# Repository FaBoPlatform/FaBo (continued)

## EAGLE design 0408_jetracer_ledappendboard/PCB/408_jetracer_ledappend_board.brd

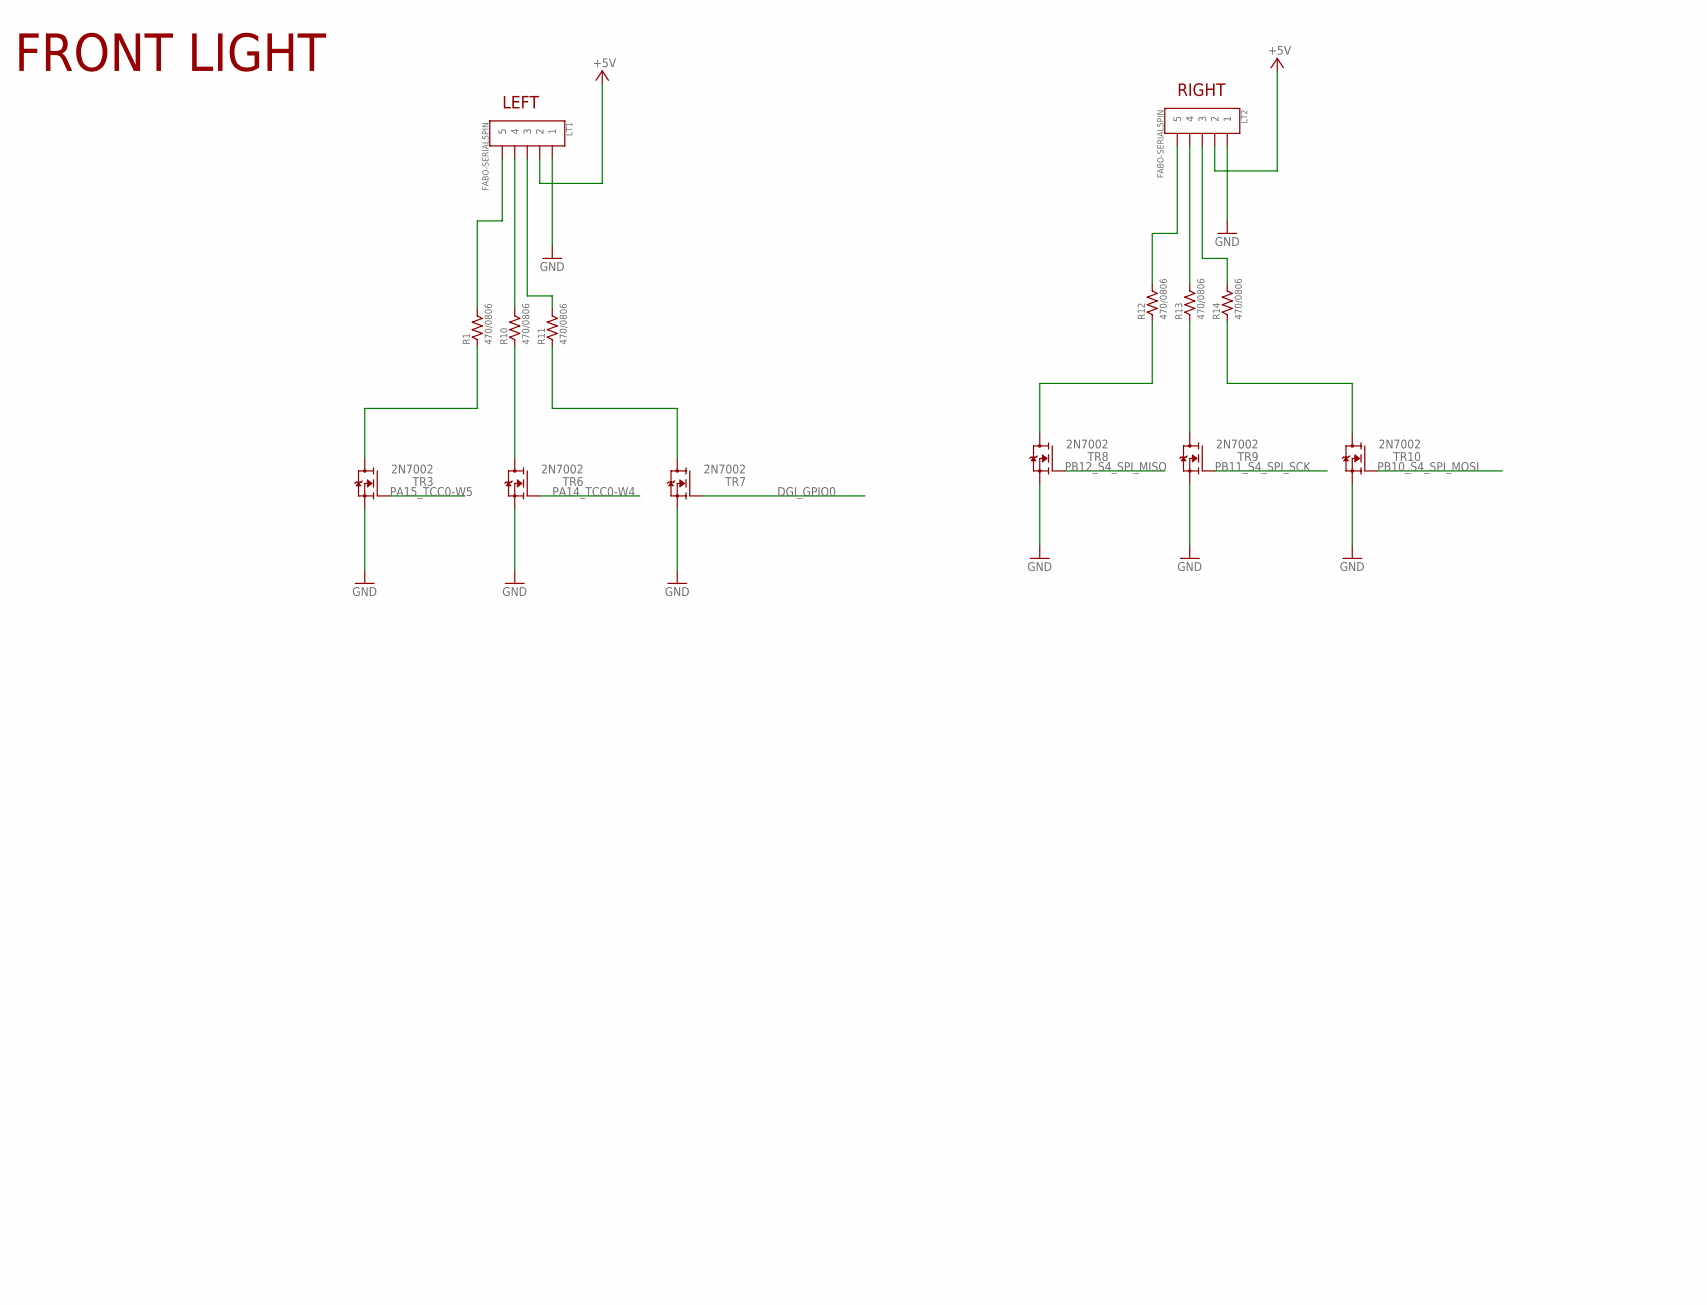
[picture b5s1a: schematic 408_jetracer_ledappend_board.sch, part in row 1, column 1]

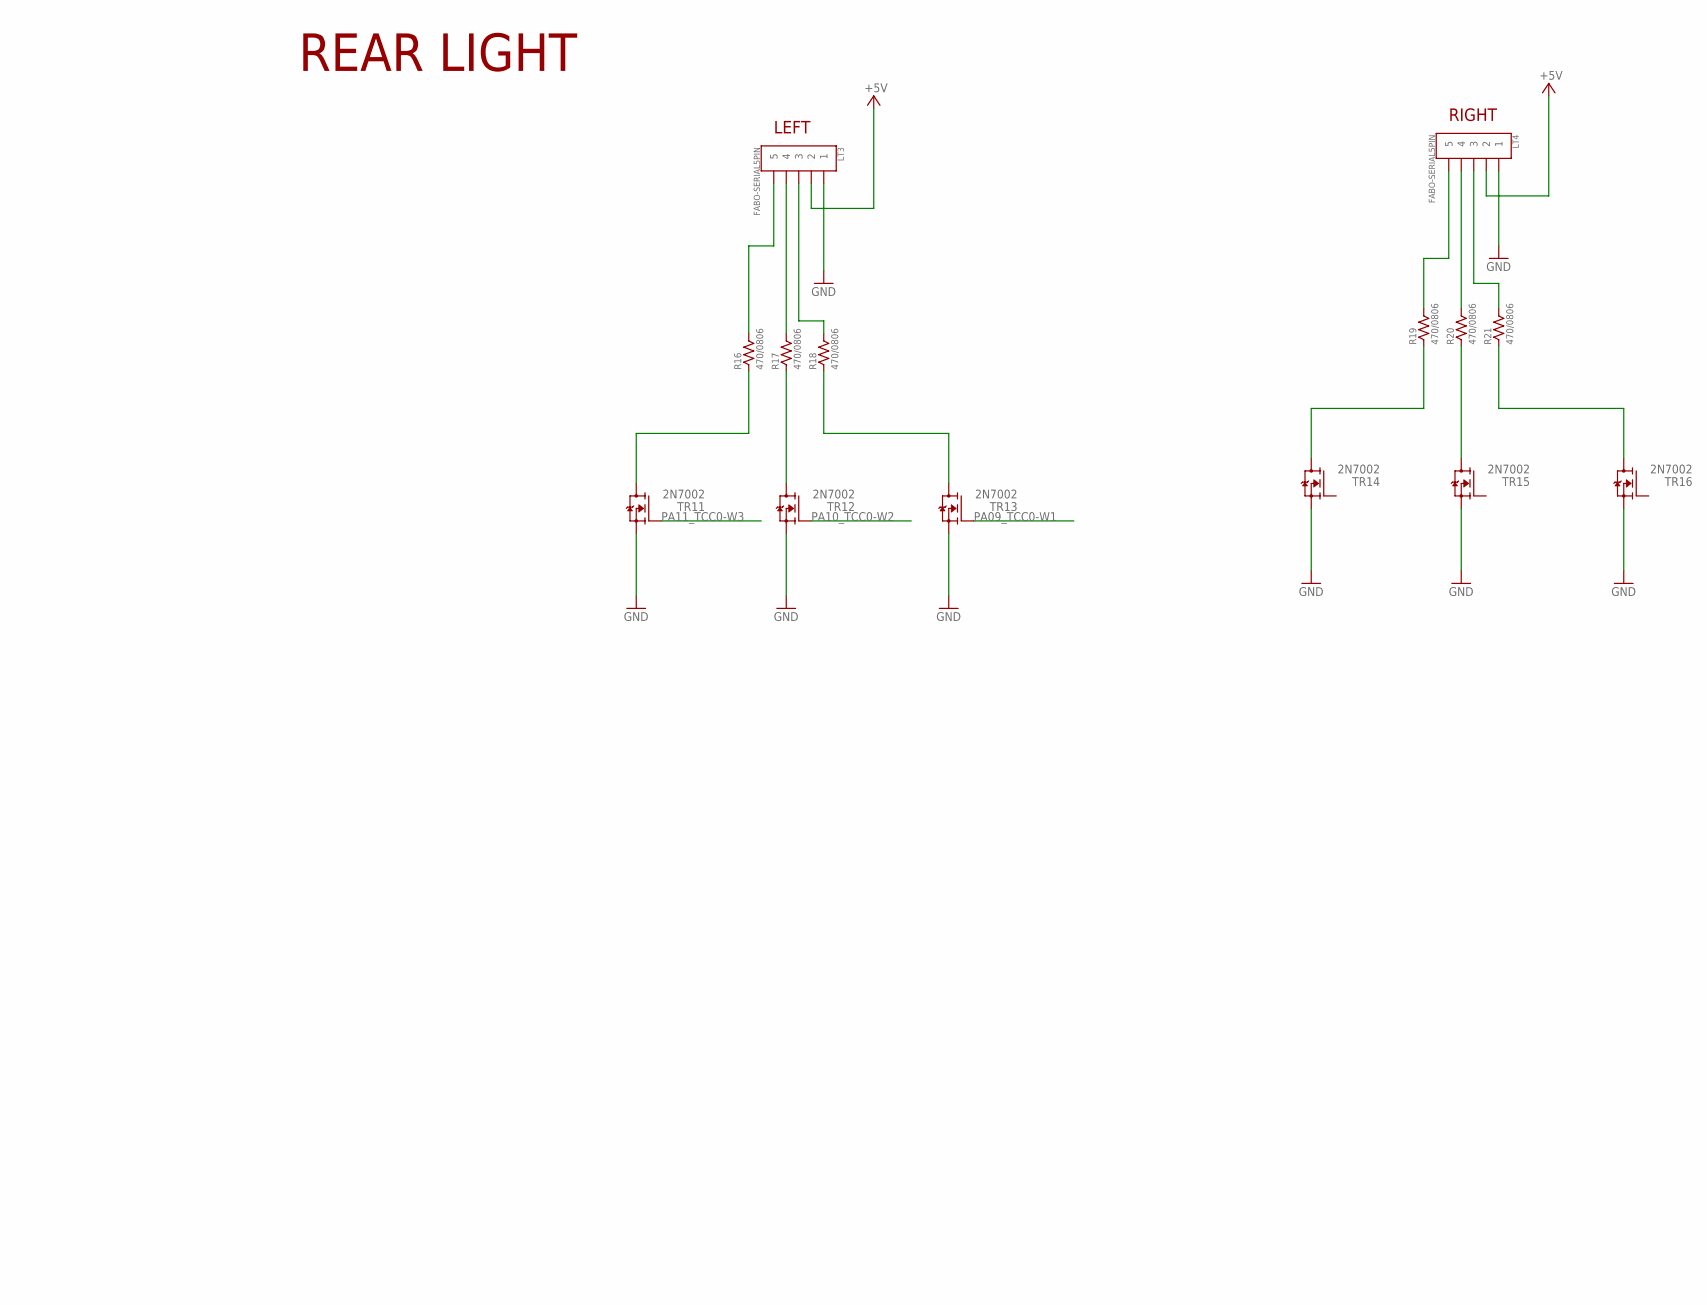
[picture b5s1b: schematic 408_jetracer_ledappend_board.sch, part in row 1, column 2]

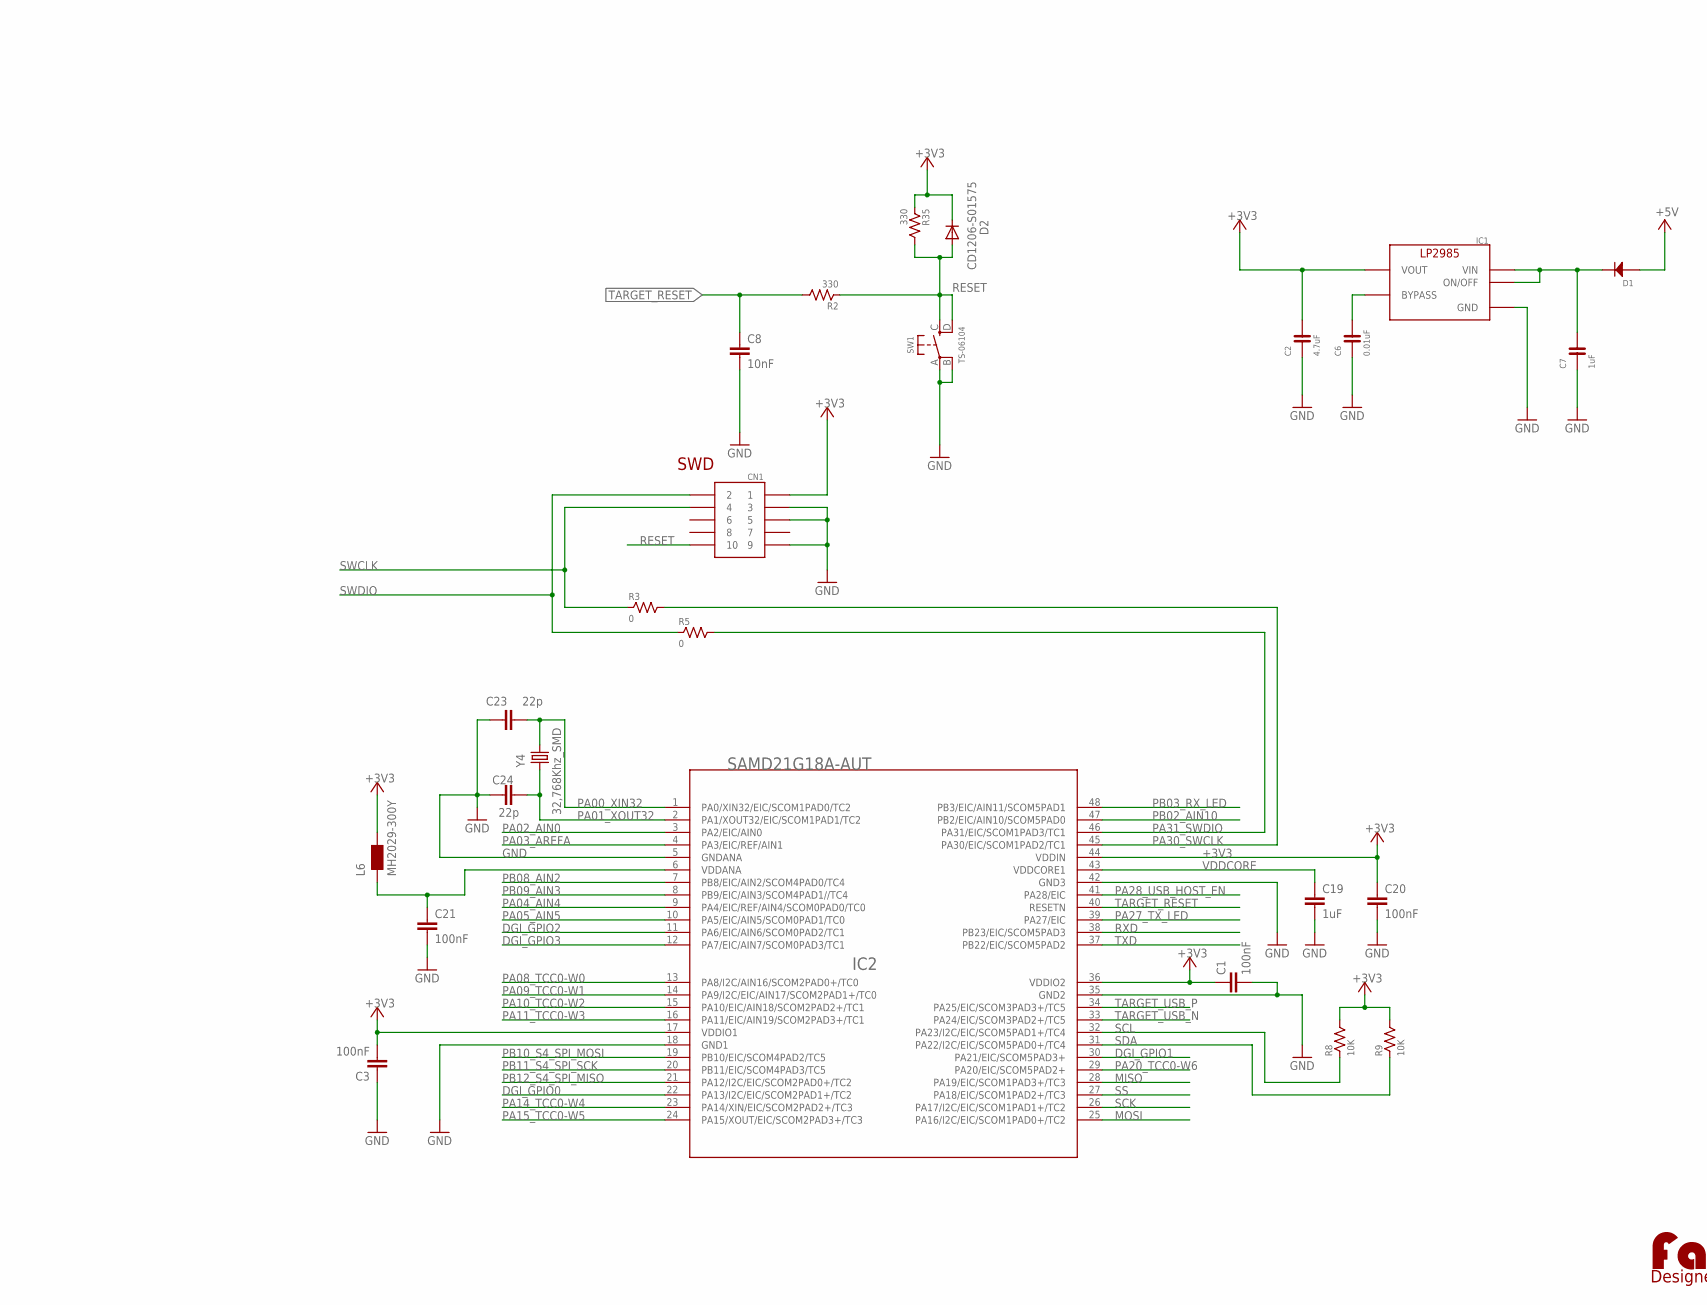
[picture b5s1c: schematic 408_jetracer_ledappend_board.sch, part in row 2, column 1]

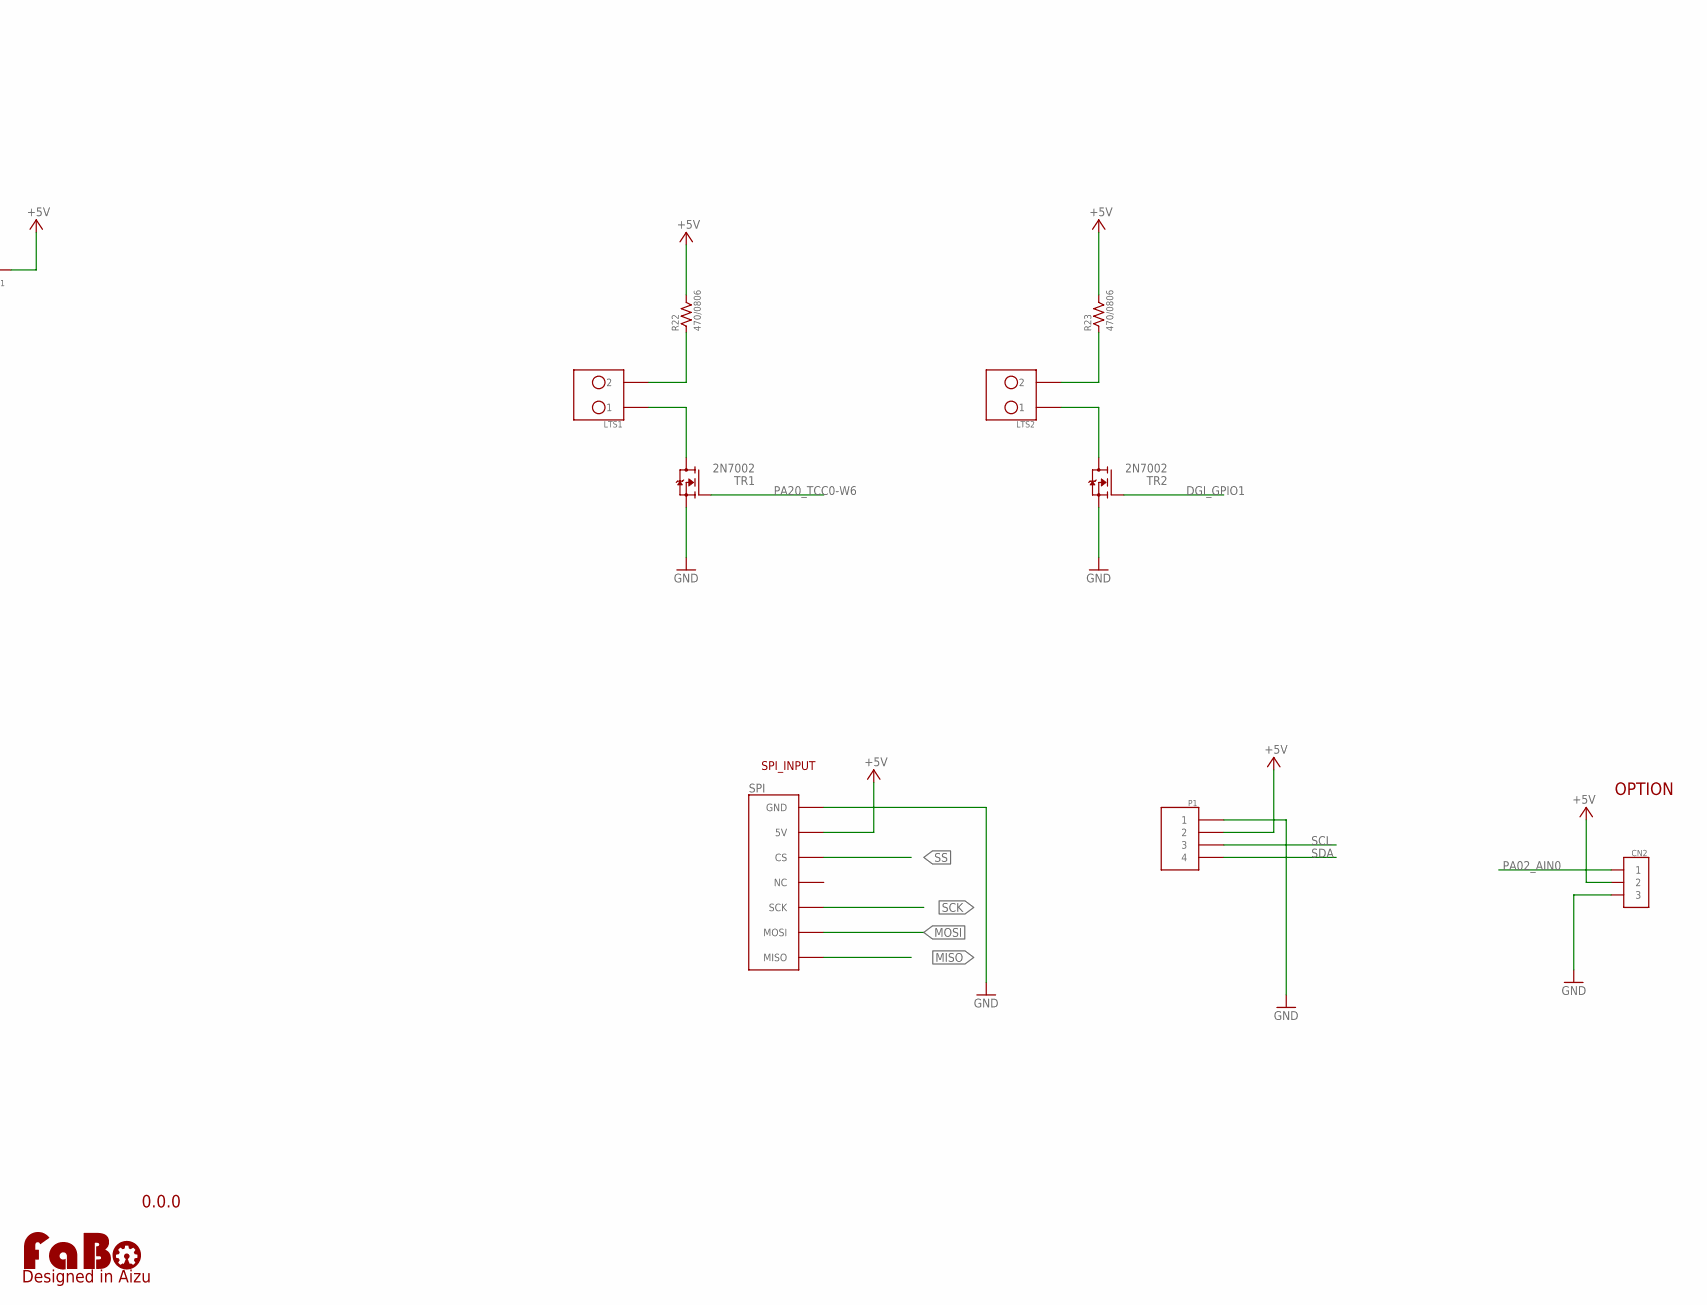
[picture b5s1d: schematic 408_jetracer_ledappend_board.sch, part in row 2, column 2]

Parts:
C1, C3, C20, C21: 100nF; C0603-ROUND
C2: 4.7uF; 0603
C6: 0.01uF; 0603
C7: 1uF; 0603
C8: 10nF; C0603-ROUND
C19: 1uF; C0603-ROUND
C23, C24: 22p; C0603-ROUND
CN1: PIN-HEADER-SMT(1.27MM)2X5
CN2: PIN_1X3
D1: DIODE-SOD-323; SOD-323
D2: CD1206-S01575; MINIMELF
IC1: LP2985-33DBV; SOT-23-5
IC2: SAMD21G18A-AUT; TQFP48-7X7
L6: MH2029-300Y; 0805
LOGO2: LOGO_FABO-M_BOTTOM; LOGO_FABO_M_BOTTOM
LT1, LT2, LT3, LT4: FABO-SERIAL5PIN; BM05B-PASS-1
LTS1, LTS2: B2B-XH-AM
P1: 4PIN_HEADER_1.25MM; 4PIN_1.25MM
R1, R10, R11, R12, R13, R14, R16, R17, R18, R19, R20, R21, R22, R23: 470/0806; 0805
R2, R35: 330; 0603
R3, R5: 0; 0603
R8, R9: 10K; 0603
SPI: FABO-7PINMULTI_SPI; BM07B-PASS-1
SW1: TS-06104
TR1, TR2, TR3, TR6, TR7, TR8, TR9, TR10, TR11, TR12, TR13, TR14, TR15, TR16: 2N7002; SOT-23
Y4: 32,768Khz_SMD; RESONATOR_EPSON_FC_145

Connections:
+3V3: C1.1, C2.2, C3.2, C20.1, CN1.1, D2.C, IC1.5 (VOUT), IC2.17 (VDDIO1), IC2.36 (VDDIO2), IC2.44 (VDDIN), L6.2, R8.2, R9.2, R35.1
+5V: CN2.2, D1.A (ANODE), LT1.2, LT2.2, LT3.2, LT4.2, P1.2, R22.2, R23.2, SPI.2 (5V)
DGI_GPIO0: IC2.22 (PA13/I2C/EIC/SCOM2PAD1+/TC2), TR7.3 (G)
DGI_GPIO1: IC2.30 (PA21/EIC/SCOM5PAD3+), TR2.3 (G)
DGI_GPIO2: IC2.11 (PA6/EIC/AIN6/SCOM0PAD2/TC1)
DGI_GPIO3: IC2.12 (PA7/EIC/AIN7/SCOM0PAD3/TC1)
GND: C1.2, C2.1, C3.1, C6.1, C7.1, C8.2, C19.2, C20.2, C21.2, C23.1, C24.1, CN1.3, CN1.5, CN1.9, CN2.3, IC1.2 (GND), IC2.5 (GNDANA), IC2.18 (GND1), IC2.35 (GND2), IC2.42 (GND3), LT1.1, LT2.1, LT3.1, LT4.1, P1.1, SPI.1 (GND), SW1.A, SW1.B, TR1.2 (S), TR2.2 (S), TR3.2 (S), TR6.2 (S), TR7.2 (S), TR8.2 (S), TR9.2 (S), TR10.2 (S), TR11.2 (S), TR12.2 (S), TR13.2 (S), TR14.2 (S), TR15.2 (S), TR16.2 (S)
MISO: IC2.28 (PA19/EIC/SCOM1PAD3+/TC3), SPI.7 (MISO)
MOSI: IC2.25 (PA16/I2C/EIC/SCOM1PAD0+/TC2), SPI.6 (MOSI)
unnamed: R13.1, TR9.1 (D)
unnamed: R10.1, TR6.1 (D)
unnamed: R1.1, TR3.1 (D)
unnamed: R11.1, TR7.1 (D)
unnamed: LT1.5, R1.2
unnamed: C6.2, IC1.4 (BYPASS)
unnamed: R12.1, TR8.1 (D)
unnamed: LT1.4, R10.2
unnamed: C21.1, IC2.6 (VDDANA), L6.1
unnamed: LT1.3, R11.2
unnamed: LT2.5, R12.2
unnamed: LT2.4, R13.2
unnamed: LT2.3, R14.2
unnamed: R14.1, TR10.1 (D)
unnamed: R17.1, TR12.1 (D)
unnamed: R16.1, TR11.1 (D)
unnamed: LTS1.2, R22.1
unnamed: LTS2.2, R23.1
unnamed: LT3.5, R16.2
unnamed: LT3.4, R17.2
unnamed: LT3.3, R18.2
unnamed: LT4.5, R19.2
unnamed: LT4.4, R20.2
unnamed: LT4.3, R21.2
unnamed: R18.1, TR13.1 (D)
unnamed: R20.1, TR15.1 (D)
unnamed: R19.1, TR14.1 (D)
unnamed: R21.1, TR16.1 (D)
unnamed: C7.2, D1.K (CATHODE), IC1.1 (VIN), IC1.3 (ON/OFF)
unnamed: LTS1.1, TR1.1 (D)
unnamed: LTS2.1, TR2.1 (D)
PA00_XIN32: C23.2, IC2.1 (PA0/XIN32/EIC/SCOM1PAD0/TC2), Y4.P$2 (2)
PA01_XOUT32: C24.2, IC2.2 (PA1/XOUT32/EIC/SCOM1PAD1/TC2), Y4.P$1 (1)
PA02_AIN0: CN2.1, IC2.3 (PA2/EIC/AIN0)
PA03_AREFA: IC2.4 (PA3/EIC/REF/AIN1)
PA04_AIN4: IC2.9 (PA4/EIC/REF/AIN4/SCOM0PAD0/TC0)
PA05_AIN5: IC2.10 (PA5/EIC/AIN5/SCOM0PAD1/TC0)
PA08_TCC0-W0: IC2.13 (PA8/I2C/AIN16/SCOM2PAD0+/TC0)
PA09_TCC0-W1: IC2.14 (PA9/I2C/EIC/AIN17/SCOM2PAD1+/TC0), TR13.3 (G)
PA10_TCC0-W2: IC2.15 (PA10/EIC/AIN18/SCOM2PAD2+/TC1), TR12.3 (G)
PA11_TCC0-W3: IC2.16 (PA11/EIC/AIN19/SCOM2PAD3+/TC1), TR11.3 (G)
PA14_TCC0-W4: IC2.23 (PA14/XIN/EIC/SCOM2PAD2+/TC3), TR6.3 (G)
PA15_TCC0-W5: IC2.24 (PA15/XOUT/EIC/SCOM2PAD3+/TC3), TR3.3 (G)
PA20_TCC0-W6: IC2.29 (PA20/EIC/SCOM5PAD2+), TR1.3 (G)
PA27_TX_LED: IC2.39 (PA27/EIC)
PA28_USB_HOST_EN: IC2.41 (PA28/EIC)
PA30_SWCLK: IC2.45 (PA30/EIC/SCOM1PAD2/TC1), R3.2
PA31_SWDIO: IC2.46 (PA31/EIC/SCOM1PAD3/TC1), R5.2
PB02_AIN10: IC2.47 (PB2/EIC/AIN10/SCOM5PAD0)
PB03_RX_LED: IC2.48 (PB3/EIC/AIN11/SCOM5PAD1)
PB08_AIN2: IC2.7 (PB8/EIC/AIN2/SCOM4PAD0/TC4)
PB09_AIN3: IC2.8 (PB9/EIC/AIN3/SCOM4PAD1//TC4)
PB10_S4_SPI_MOSI: IC2.19 (PB10/EIC/SCOM4PAD2/TC5), TR10.3 (G)
PB11_S4_SPI_SCK: IC2.20 (PB11/EIC/SCOM4PAD3/TC5), TR9.3 (G)
PB12_S4_SPI_MISO: IC2.21 (PA12/I2C/EIC/SCOM2PAD0+/TC2), TR8.3 (G)
RESET: CN1.10, D2.A, R2.1, R35.2, SW1.C, SW1.D
RXD: IC2.38 (PB23/EIC/SCOM5PAD3)
SCK: IC2.26 (PA17/I2C/EIC/SCOM1PAD1+/TC2), SPI.5 (SCK)
SCL: IC2.32 (PA23/I2C/EIC/SCOM5PAD1+/TC4), P1.3, R8.1
SDA: IC2.31 (PA22/I2C/EIC/SCOM5PAD0+/TC4), P1.4, R9.1
SS: IC2.27 (PA18/EIC/SCOM1PAD2+/TC3), SPI.3 (CS)
SWCLK: CN1.4, R3.1
SWDIO: CN1.2, R5.1
TARGET_RESET: C8.1, IC2.40 (RESETN), R2.2
TARGET_USB_N: IC2.33 (PA24/EIC/SCOM3PAD2+/TC5)
TARGET_USB_P: IC2.34 (PA25/EIC/SCOM3PAD3+/TC5)
TXD: IC2.37 (PB22/EIC/SCOM5PAD2)
VDDCORE: C19.1, IC2.43 (VDDCORE1)

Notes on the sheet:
0.0.0
SPI_INPUT
FRONT LIGHT
LEFT
RIGHT
REAR LIGHT
SWD
OPTION

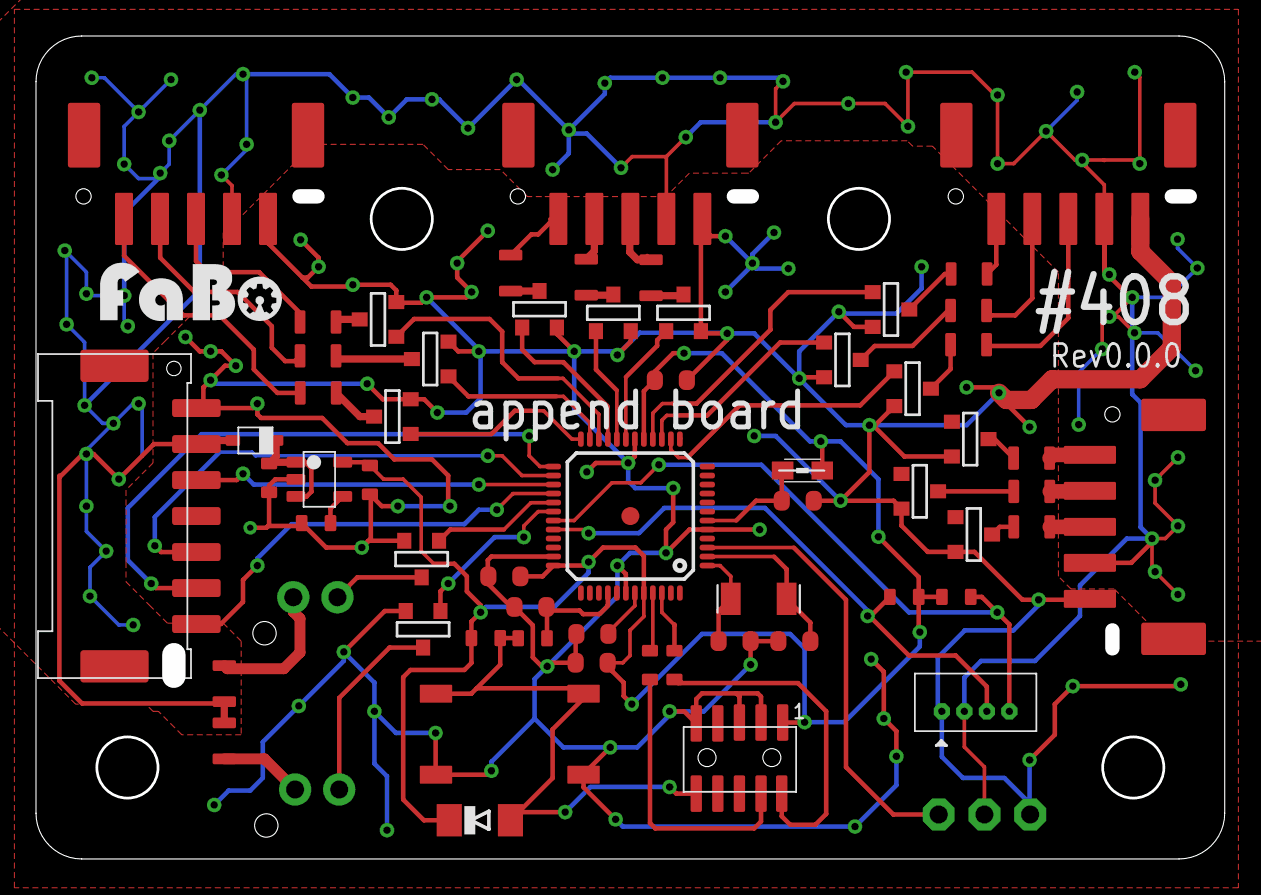
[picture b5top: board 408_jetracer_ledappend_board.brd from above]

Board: 2 copper layers, 66.0 x 45.7 mm, 63 parts (1 on the bottom side), 61 nets.
